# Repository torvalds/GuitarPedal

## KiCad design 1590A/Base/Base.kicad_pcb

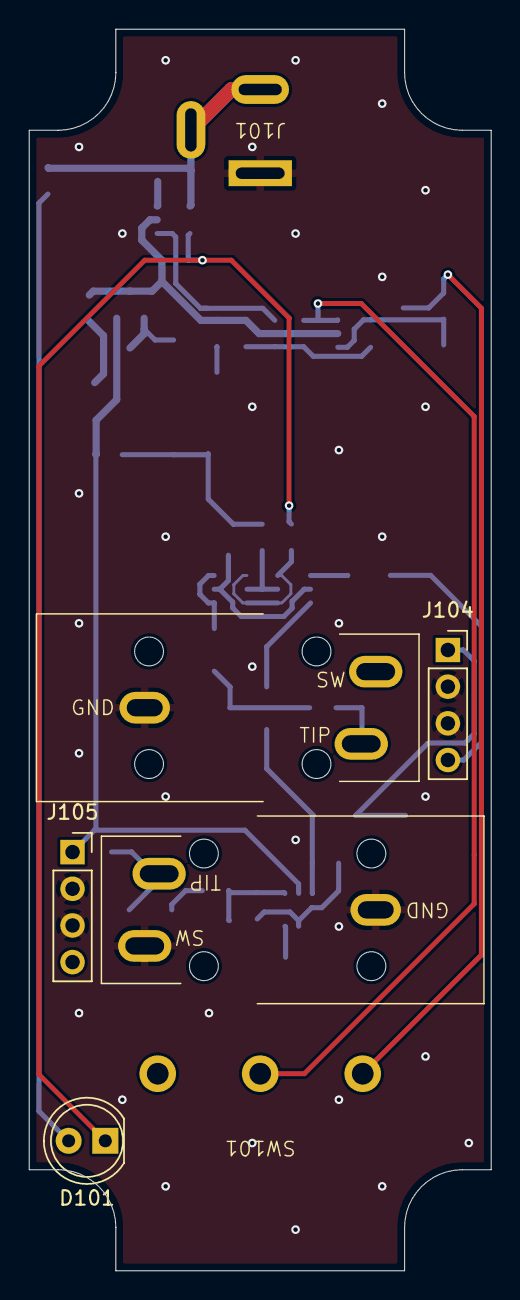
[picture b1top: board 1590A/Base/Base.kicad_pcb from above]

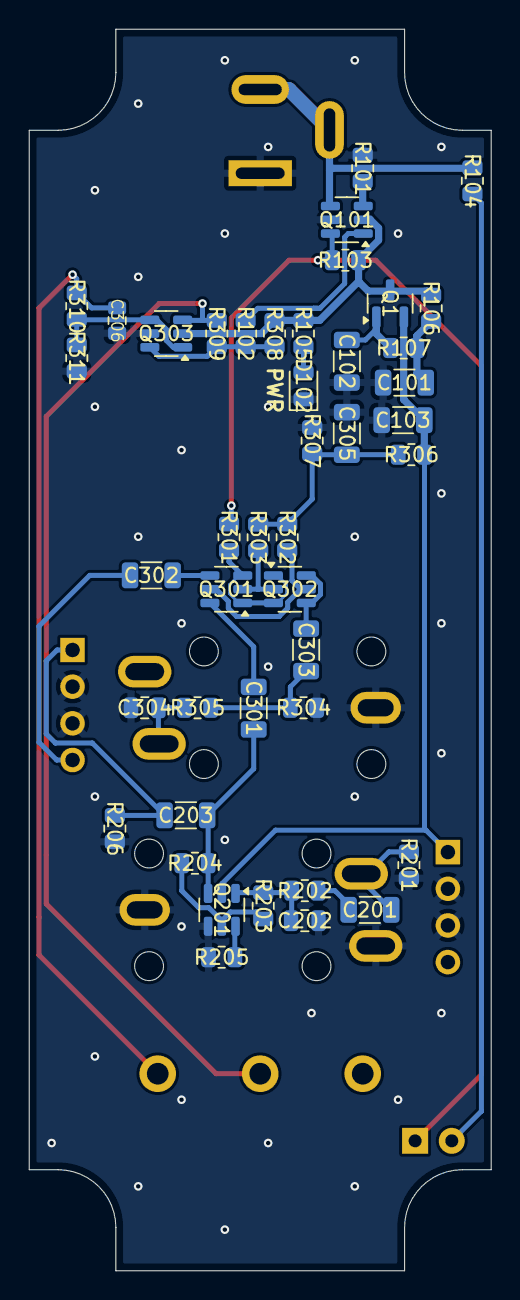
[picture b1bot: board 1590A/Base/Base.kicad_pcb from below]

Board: 2 copper layers, 32.0 x 86.0 mm, 51 parts (43 on the bottom side), 32 nets.

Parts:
Box101: 1590A
C101, C102, C103, C305: 10uF; C_1206_3216Metric
C201, C203: 4.7uF; C_1206_3216Metric
C202: 150pF; C_0805_2012Metric
C301, C302, C303: 1uF; C_1206_3216Metric
C304: 220pF; C_0805_2012Metric
C306: 0.1uF; C_0704_1810Metric
D101: LED; LED_D5.0mm
D102: LED; LED_0805_2012Metric
J101: Barrel_Jack_Switch; Wurth WR-DC 2.1mm Power Jack
J102, J103: AudioJack2_Ground; CK-6.35
J104, J105: Conn_01x04_Pin; PinSocket_1x04_P2.54mm_Vertical
Q1: BC846; SOT-23
Q101, Q301, Q302, Q303: DMC3071LVT; TSOT-23-6
Q201: LS844; SOT-23-6
R101, R102, R103: 100k; R_0805_2012Metric
R104, R105, R106, R107, R305: 2k2; R_0805_2012Metric
R201, R203, R206, R302, R303, R304, R310: 1MEG; R_0805_2012Metric
R202: 1k; R_0805_2012Metric
R204, R205: 1k5; R_0805_2012Metric
R301: 10MEG; R_0805_2012Metric
R306, R307: 4k7; R_0805_2012Metric
R308, R309, R311: 22k; R_0805_2012Metric
SW101: SW_Push_SPDT; PBS-24-102P

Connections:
+VA: C103.1, J105.1, Q1.2 (E), Q201.2 (D), R306.2
BUFFERED: C203.1, C301.1, Q201.3 (S), R204.1
GATE: Q301.1 (G), Q301.3 (G), Q302.1 (G), Q302.3 (G), R301.2
GND: C101.2, C102.2, C103.2, C202.2, C304.2, C305.1, C306.2, D102.1 (K), J101.1, J102.G, J102.S, J103.G, J104.2, J104.3, J105.2, J105.3, Q101.5 (S), Q201.4 (G), Q303.5 (S), R101.2, R201.2, R205.2, R206.2, R304.1, R307.1, R311.1
IN^{CONN}: C201.1, J102.T, R201.1
IN^{EFF}: C203.2, J104.1, R206.1
unnamed: C101.1, R106.2, R107.1
unnamed: C201.2, R202.1
unnamed: C303.2, R304.2, R305.1
unnamed: D101.2 (A), R104.2
unnamed: D102.2 (A), R105.2
unnamed: C102.1, Q1.1 (B), R107.2
unnamed: Q101.1 (G), R102.2
unnamed: Q101.3 (G), R101.1
unnamed: C202.1, Q201.1 (G), R202.2, R203.1
unnamed: Q201.5 (D), R203.2, R204.2
unnamed: Q201.6 (S), R205.1
unnamed: C301.2, Q301.6 (D)
unnamed: Q301.5 (S), Q302.5 (S), R302.1
unnamed: C302.2, Q301.4 (D)
unnamed: Q301.2 (S), Q302.2 (S), R303.2
unnamed: C303.1, Q302.4 (D), Q302.6 (D)
unnamed: Q303.1 (G), Q303.4 (D), R310.2, R311.2
ON_LOW: D101.1 (K), Q101.6 (D), R103.2, R301.1
ON_OFF: Q303.6 (D), R102.1, R308.1, R309.1
OUT^{CONN}: C304.1, J103.T, R305.2
OUT^{EFF}: C302.1, J104.4
PWRIN: J101.2, J101.3, Q101.4 (D), R104.1
SW1: Q303.3 (G), R309.2, SW101.2 (B)
SW2: C306.1, R310.1, SW101.3 (C)
VBIAS: C305.2, R302.2, R303.1, R306.1, R307.2
VIN: Q1.3 (C), Q101.2 (S), Q303.2 (S), R103.1, R105.1, R106.1, R308.2

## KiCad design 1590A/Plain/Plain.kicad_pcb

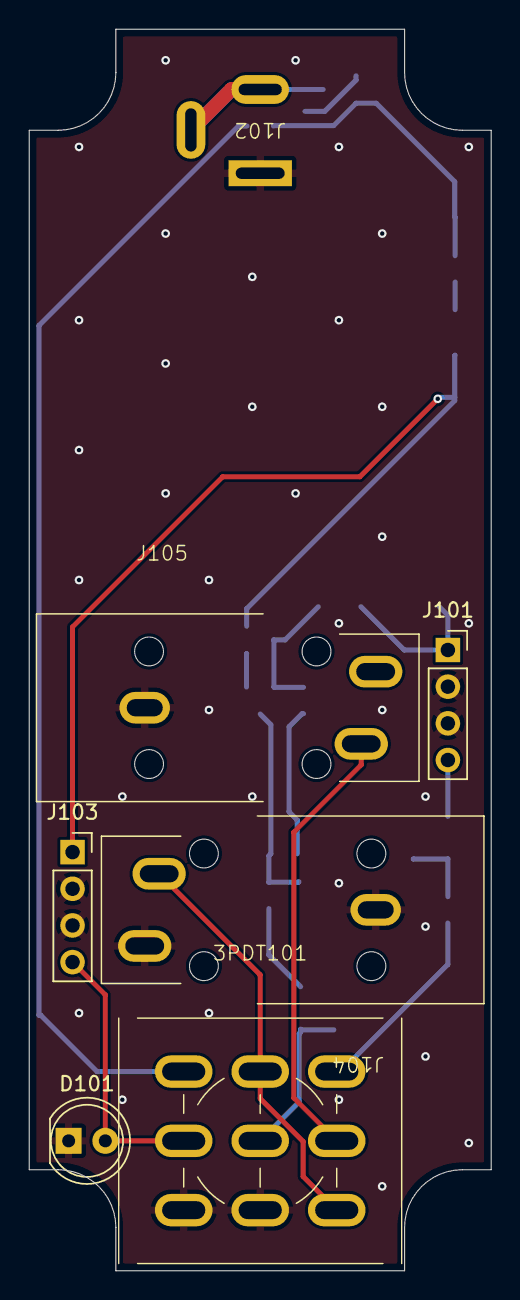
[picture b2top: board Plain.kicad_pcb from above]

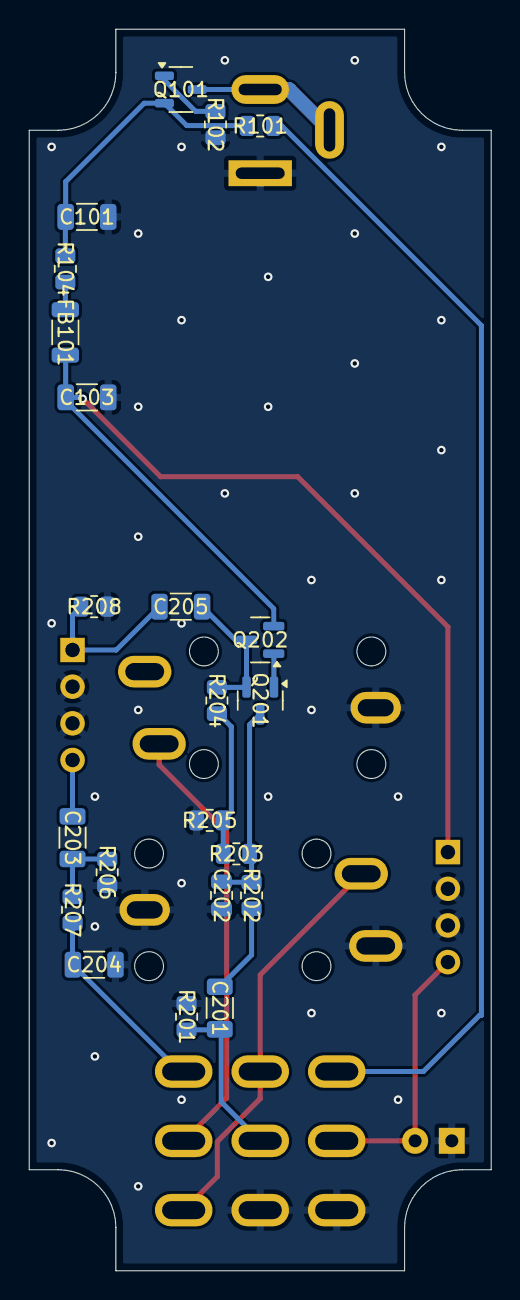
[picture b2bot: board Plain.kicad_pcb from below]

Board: 2 copper layers, 32.0 x 86.0 mm, 30 parts (22 on the bottom side), 20 nets.

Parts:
3PDT101: 3PDT-Stomp-Switch
Box101: 1590A
C101, C103: 22uF; C_1206_3216Metric
C201, C203, C205: 1uF; C_1206_3216Metric
C202: 150pF; C_0805_2012Metric
C204: 1nF; C_1206_3216Metric
D101: LED; LED_D5.0mm
FB101: FerriteBead; L_1206_3216Metric
J101, J103: Conn_01x04_Pin; PinSocket_1x04_P2.54mm_Vertical
J102: Barrel_Jack_Switch; Wurth WR-DC 2.1mm Power Jack
J104: Input; CK-6.35
J105: Output; CK-6.35
Q101: PMV250; SOT-23-3
Q201: MMBF5103; SOT-23
Q202: BC857C; SOT-23
R101, R207: 3k3; R_0805_2012Metric
R102: 100k; R_0805_2012Metric
R104: 100R; R_0805_2012Metric
R201, R203, R206, R208: 1MEG; R_0805_2012Metric
R202: 1k; R_0805_2012Metric
R204, R205: 2k2; R_0805_2012Metric

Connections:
+VA: C103.1, FB101.2, J103.1, Q202.2 (E)
GND: 3PDT101.3 (A3), 3PDT101.6 (B3), C101.2, C103.2, C202.2, C204.1, D101.1 (K), J101.2, J101.3, J102.1, J103.2, J103.3, J104.S, J104.TN, J105.S, R102.2, R201.2, R205.2, R206.2, R208.2
INPUT: 3PDT101.5 (B2), C201.1, R201.1
IN^{CONN}: 3PDT101.4 (B1), 3PDT101.9 (C3), J104.T
IN^{EFF}: C205.2, J101.1, R208.1
LEDPWR: 3PDT101.2 (A2), D101.2 (A), J103.4
unnamed: 3PDT101.1 (A1), R101.1
unnamed: C201.2, R202.1
unnamed: C203.2, R206.1, R207.1
unnamed: FB101.1, R104.2
unnamed: Q101.1 (G), R102.1
unnamed: Q201.1 (D), Q202.1 (B)
unnamed: C202.1, Q201.3 (G), R202.2, R203.1
unnamed: C205.1, Q201.2 (S), Q202.3 (C), R204.1
unnamed: R203.2, R204.2, R205.1
OUTPUT: 3PDT101.7 (C1), C204.2, R207.2
OUT^{CONN}: 3PDT101.8 (C2), J105.T
OUT^{EFF}: C203.1, J101.4
PWRIN: J102.2, J102.3, Q101.3 (D)
VIN: C101.1, Q101.2 (S), R101.2, R104.1

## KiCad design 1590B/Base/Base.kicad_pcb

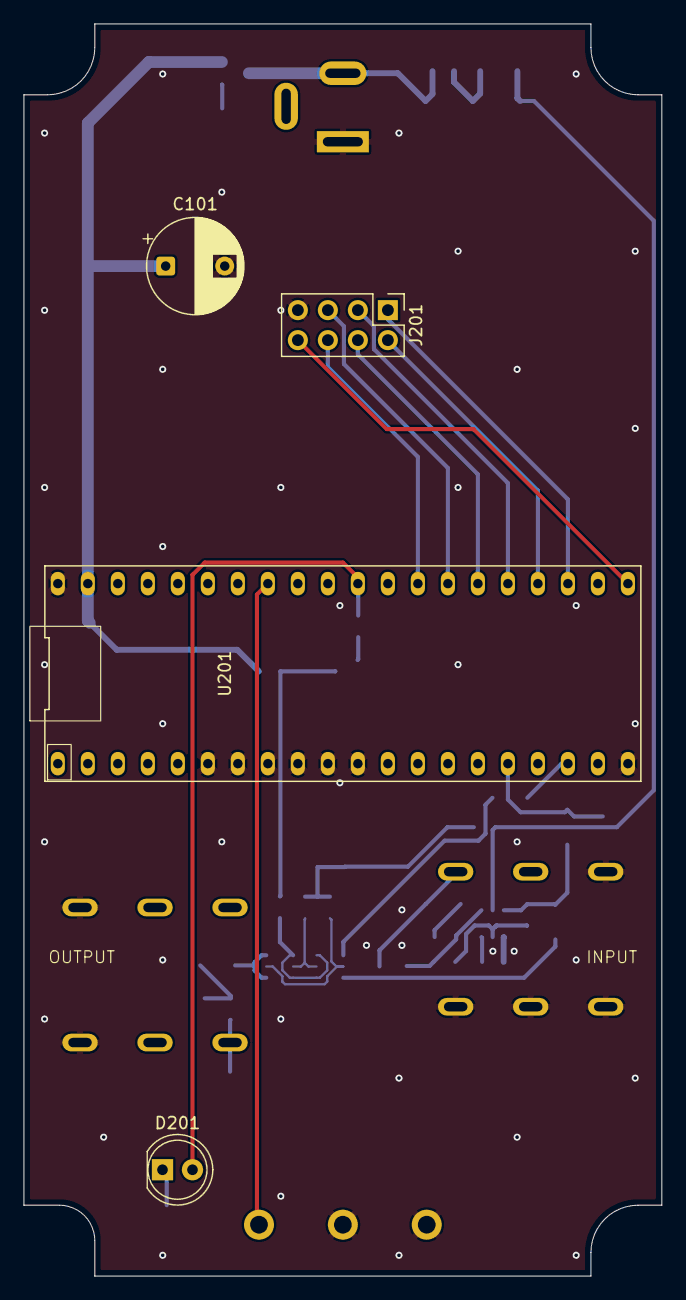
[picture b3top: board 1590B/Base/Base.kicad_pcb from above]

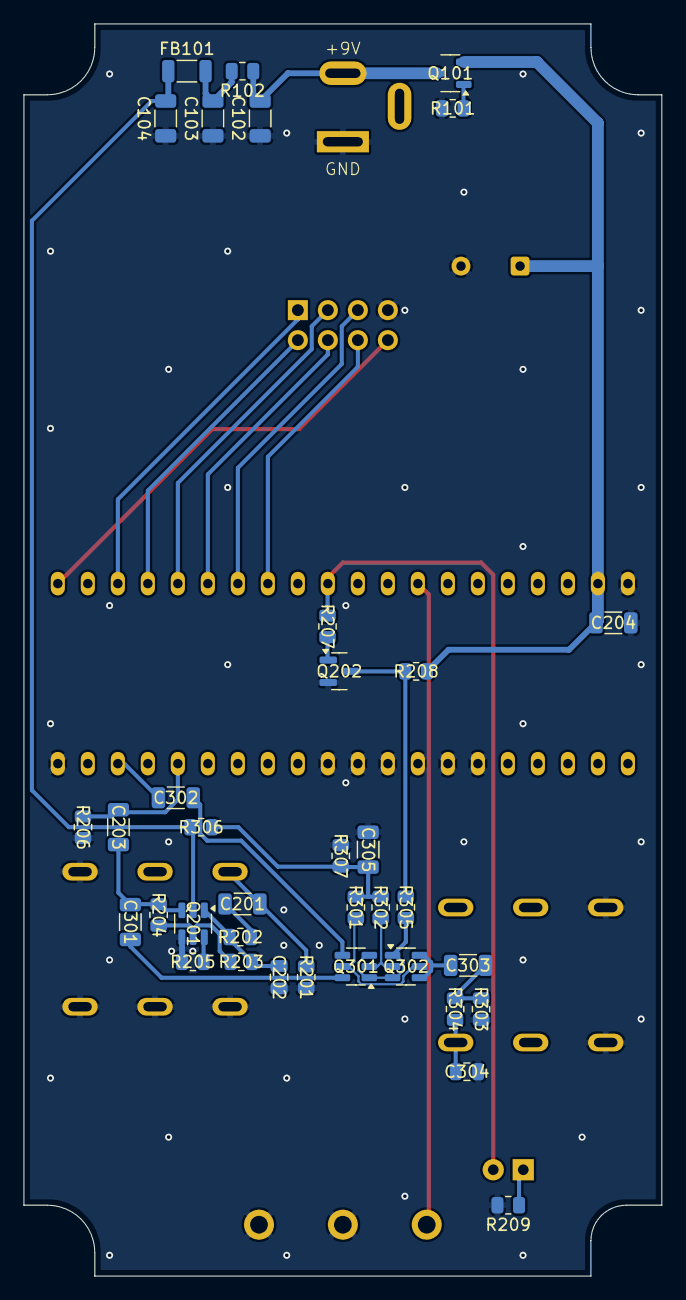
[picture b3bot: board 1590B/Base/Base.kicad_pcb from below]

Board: 2 copper layers, 54.0 x 106.0 mm, 45 parts (36 on the bottom side), 35 nets.

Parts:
Box101: 1590B
C101: 100uF; CP_Radial_D8.0mm_P5.00mm
C102, C103, C305: 10uF; C_1206_3216Metric
C104, C301, C302, C303: 1uF; C_1206_3216Metric
C201, C203: 4.7uF; C_1206_3216Metric
C202: 150pF; C_0805_2012Metric
C204: 47uF; C_1206_3216Metric
C304: 1nF; C_0805_2012Metric
D201: LED; LED_D5.0mm
FB101: FerriteBead; L_1206_3216Metric
J101: Barrel_Jack_Switch; Wurth WR-DC 2.1mm Power Jack
J102, J103: AudioJack3_SwitchTR; NRJ6HM-1-PRE
J201: Conn_02x04_Odd_Even; PinHeader_2x04_P2.54mm_Vertical
Q101: PMV250; SOT-23-3
Q201: LS844; SOT-23-6
Q202: BC846; SOT-23
Q301, Q302: DMC3071LVT; TSOT-23-6
R101, R208: 100k; R_0805_2012Metric
R102: 100R; R_0805_2012Metric
R201, R203, R206, R301, R302, R303: 1MEG; R_0805_2012Metric
R202, R209: 1k; R_0805_2012Metric
R204, R205: 1k5; R_0805_2012Metric
R207: 10k; R_0805_2012Metric
R304: 3k3; R_0805_2012Metric
R305: 10MEG; R_0805_2012Metric
R306, R307: 4k7; R_0805_2012Metric
SW201: SW_Push_SPDT; PBS-24-102P
U201: Daisy Seed; DaisySeed

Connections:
+3.3VA: J201.8, U201.21 (+3V3_A)
+VA: C104.2, FB101.1, Q201.2 (D), R306.2
BUFFERED: C203.1, C301.1, Q201.3 (S), R204.1
FOOTSW: SW201.3 (C), U201.33 (FOOT_SW2)
GATE: Q301.1 (G), Q301.3 (G), Q302.1 (G), Q302.3 (G), R305.2
GND: C101.2, C102.1, C103.1, C104.1, C202.2, C204.2, C304.2, C305.1, J101.1, J102.RN, J102.S, J102.TN, J103.S, J201.7, Q201.4 (G), Q202.2 (E), R101.2, R201.2, R205.2, R206.2, R209.2, R303.1, R307.1, SW201.1 (A), SW201.2 (B), U201.6 (SW3_UP), U201.7 (SW3_DN), U201.8 (SW2_UP), U201.9 (SW2_DN), U201.10 (SW1_UP), U201.11 (SW1_DN), U201.20 (AGND), U201.40 (GND)
IN^{CONN}: C201.1, J102.T, R201.1
IN^{EFF}: C203.2, R206.1, U201.16 (AUDIO_IN_L)
unnamed: C103.2, FB101.2, R102.2
unnamed: C201.2, R202.1
unnamed: C303.2, R303.2, R304.1
unnamed: D201.1 (K), R209.1
unnamed: Q101.1 (G), R101.1
unnamed: C202.1, Q201.1 (G), R202.2, R203.1
unnamed: Q201.5 (D), R203.2, R204.2
unnamed: Q201.6 (S), R205.1
unnamed: Q202.1 (B), R207.2
unnamed: C301.2, Q301.6 (D)
unnamed: Q301.5 (S), Q302.5 (S), R301.1
unnamed: C302.2, Q301.4 (D)
unnamed: Q301.2 (S), Q302.2 (S), R302.2
unnamed: C303.1, Q302.4 (D), Q302.6 (D)
ON_LOW: Q202.3 (C), R208.2, R305.1
ON_OFF: D201.2 (A), R207.1, U201.30 (LED_2)
OUT^{CONN}: C304.1, J103.T, R304.2
OUT^{EFF}: C302.1, U201.18 (AUDIO_OUT_L)
POT1: J201.1, U201.23 (POT1)
POT2: J201.2, U201.24 (POT2)
POT3: J201.3, U201.25 (POT3)
POT4: J201.4, U201.26 (POT4)
POT5: J201.5, U201.27 (POT5)
POT6: J201.6, U201.28 (POT6)
PWRIN: C102.2, J101.2, Q101.3 (D), R102.1
VBIAS: C305.2, R301.2, R302.1, R306.1, R307.2
VIN: C101.1, C204.1, Q101.2 (S), R208.1, U201.39 (V_IN)

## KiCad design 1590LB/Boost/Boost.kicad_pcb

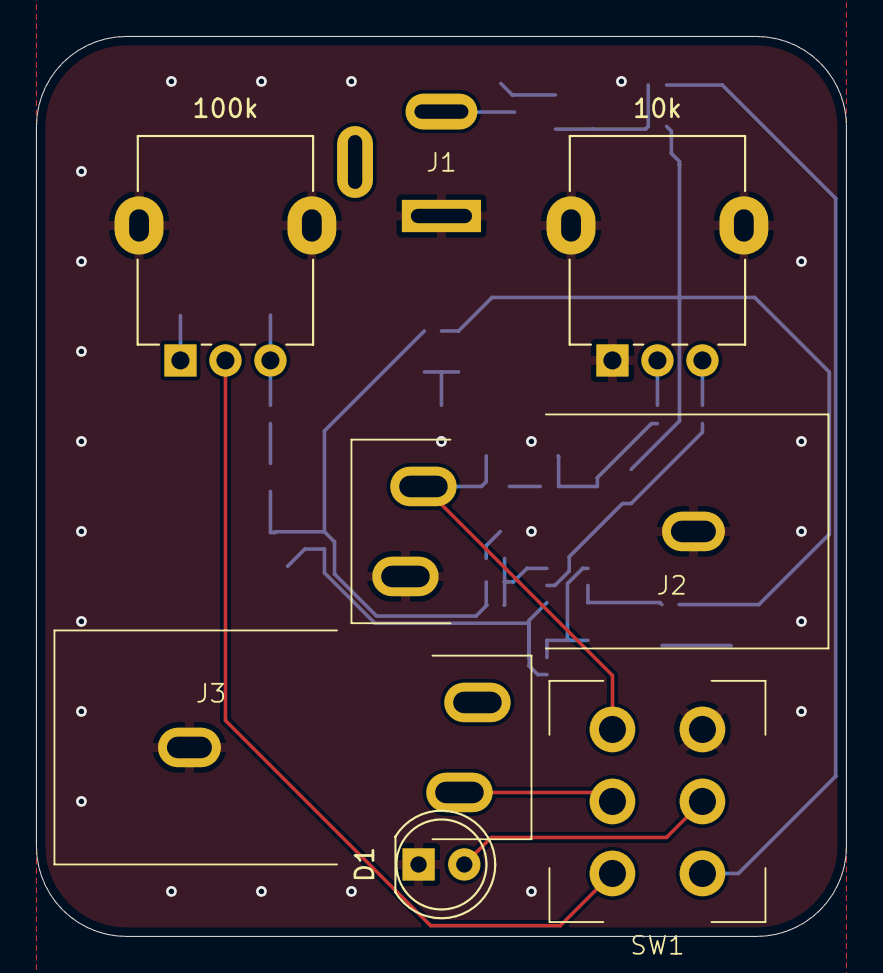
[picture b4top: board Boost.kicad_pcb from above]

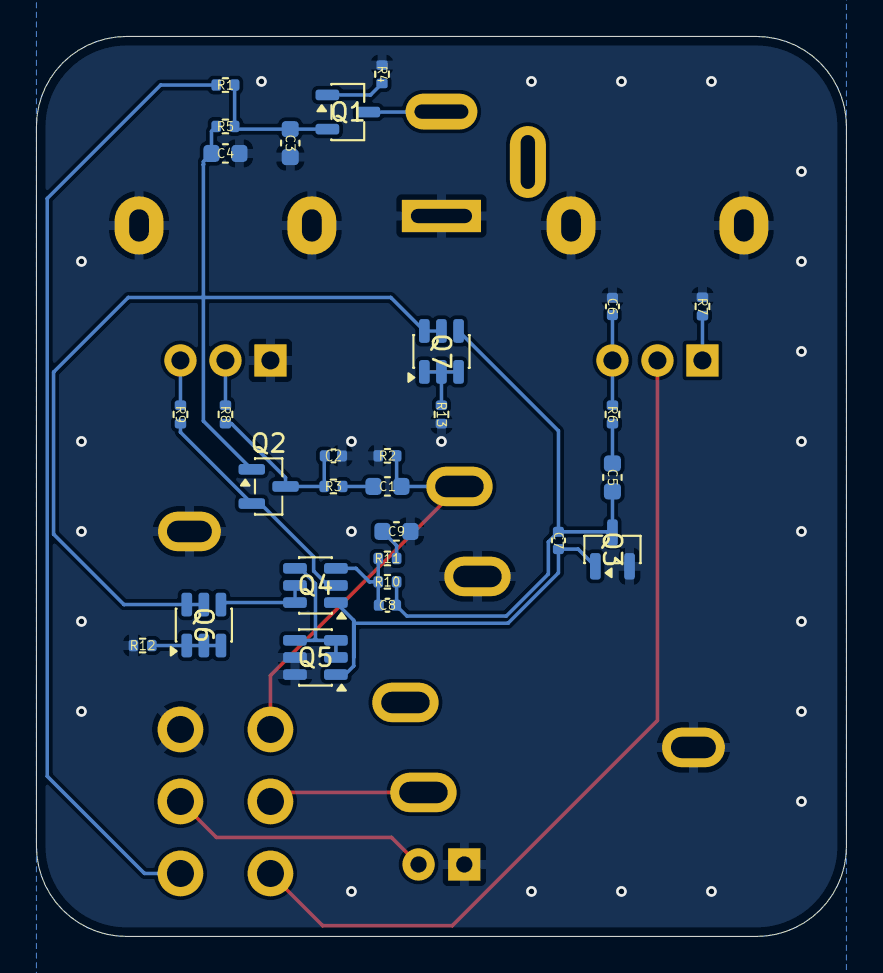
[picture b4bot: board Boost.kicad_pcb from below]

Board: 2 copper layers, 45.0 x 50.0 mm, 36 parts (29 on the bottom side), 26 nets.

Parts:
C1, C5: 1uF; C_0603_1608Metric
C2, C8: 150pF; C_0402_1005Metric
C3, C4, C9: 10uF; C_0603_1608Metric
C6, C7: 1nF; C_0402_1005Metric
D1: LED; LED_D5.0mm
J1: Barrel_Jack_Switch; Wurth WR-DC 2.1mm Power Jack
J2, J3: AudioJack2_SwitchT; CK-6.35-no-NPTH
Q1: PMV250; SOT-23-3
Q2: MMBFJ309L; SOT-23
Q3: BC849C; SOT-23
Q4, Q6, Q7: DMMT5401; SOT-23-6
Q5: DMMT5551; SOT-23-6
R1, R6: 3k3; R_0402_1005Metric
R2, R8: 1MEG; R_0402_1005Metric
R3: 1k; R_0402_1005Metric
R4, R10: 100k; R_0402_1005Metric
R5: 33R; R_0402_1005Metric
R7, R11: 10k; R_0402_1005Metric
R9: 2k2; R_0402_1005Metric
R12, R13: 5k1; R_0402_1005Metric
RV1: 100k; Potentiometer_9mm_MP
RV2: 10k; Potentiometer_9mm_MP
SW1: SW_DPDT_x2; FS5700DPMT2B2M2QE

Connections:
+VA: C4.2, Q2.1 (D), Q6.5 (E), Q6.6 (E), Q7.5 (E), Q7.6 (E), R5.1
BUFFERED: Q2.2 (S), Q4.2 (B), R9.1
FEEDBACK: C8.1, Q4.3 (B), R10.1, R11.1
GND: C2.2, C3.1, C4.1, C6.1, C9.1, D1.1 (K), J1.1, J2.S, J2.TN, J3.S, Q3.2 (E), Q5.5 (E), Q5.6 (E), R2.2, R4.2, R7.2, R12.2, R13.2, RV1.MP (MountPin), RV2.1, RV2.MP (MountPin), SW1.1 (A)
INPUT: C2.1, Q2.3 (G), R3.2, R8.1
IN^{CONN}: C1.1, J2.T, R2.1, SW1.4 (A)
LTP_OUT: C7.2, Q3.1 (B), Q4.1 (C), Q5.1 (C)
unnamed: C1.2, R3.1
unnamed: C5.2, R6.1
unnamed: C6.2, R6.2, RV1.3
unnamed: C9.2, R11.2
unnamed: D1.2 (A), SW1.2 (B)
unnamed: Q1.1 (G), R4.1
unnamed: Q4.4 (C), Q5.2 (B), Q5.3 (B), Q5.4 (C)
unnamed: Q6.1 (C), Q6.2 (B), Q6.3 (B), R12.1
unnamed: Q7.1 (C), Q7.2 (B), Q7.3 (B), R13.1
unnamed: R7.1, RV1.1
unnamed: R8.2, RV2.2
unnamed: R9.2, RV2.3
unnamed: R1.2, SW1.3 (C)
OUTPUT: C5.1, C7.1, C8.2, Q3.3 (C), Q7.4 (C), R10.2
OUT^{CONN}: J3.T, SW1.5 (B)
OUT^{STOMP}: RV1.2, SW1.6 (C)
PWRIN: J1.2, Q1.3 (D)
SRC1: Q4.5 (E), Q4.6 (E), Q6.4 (C)
VIN: C3.2, Q1.2 (S), R1.1, R5.2

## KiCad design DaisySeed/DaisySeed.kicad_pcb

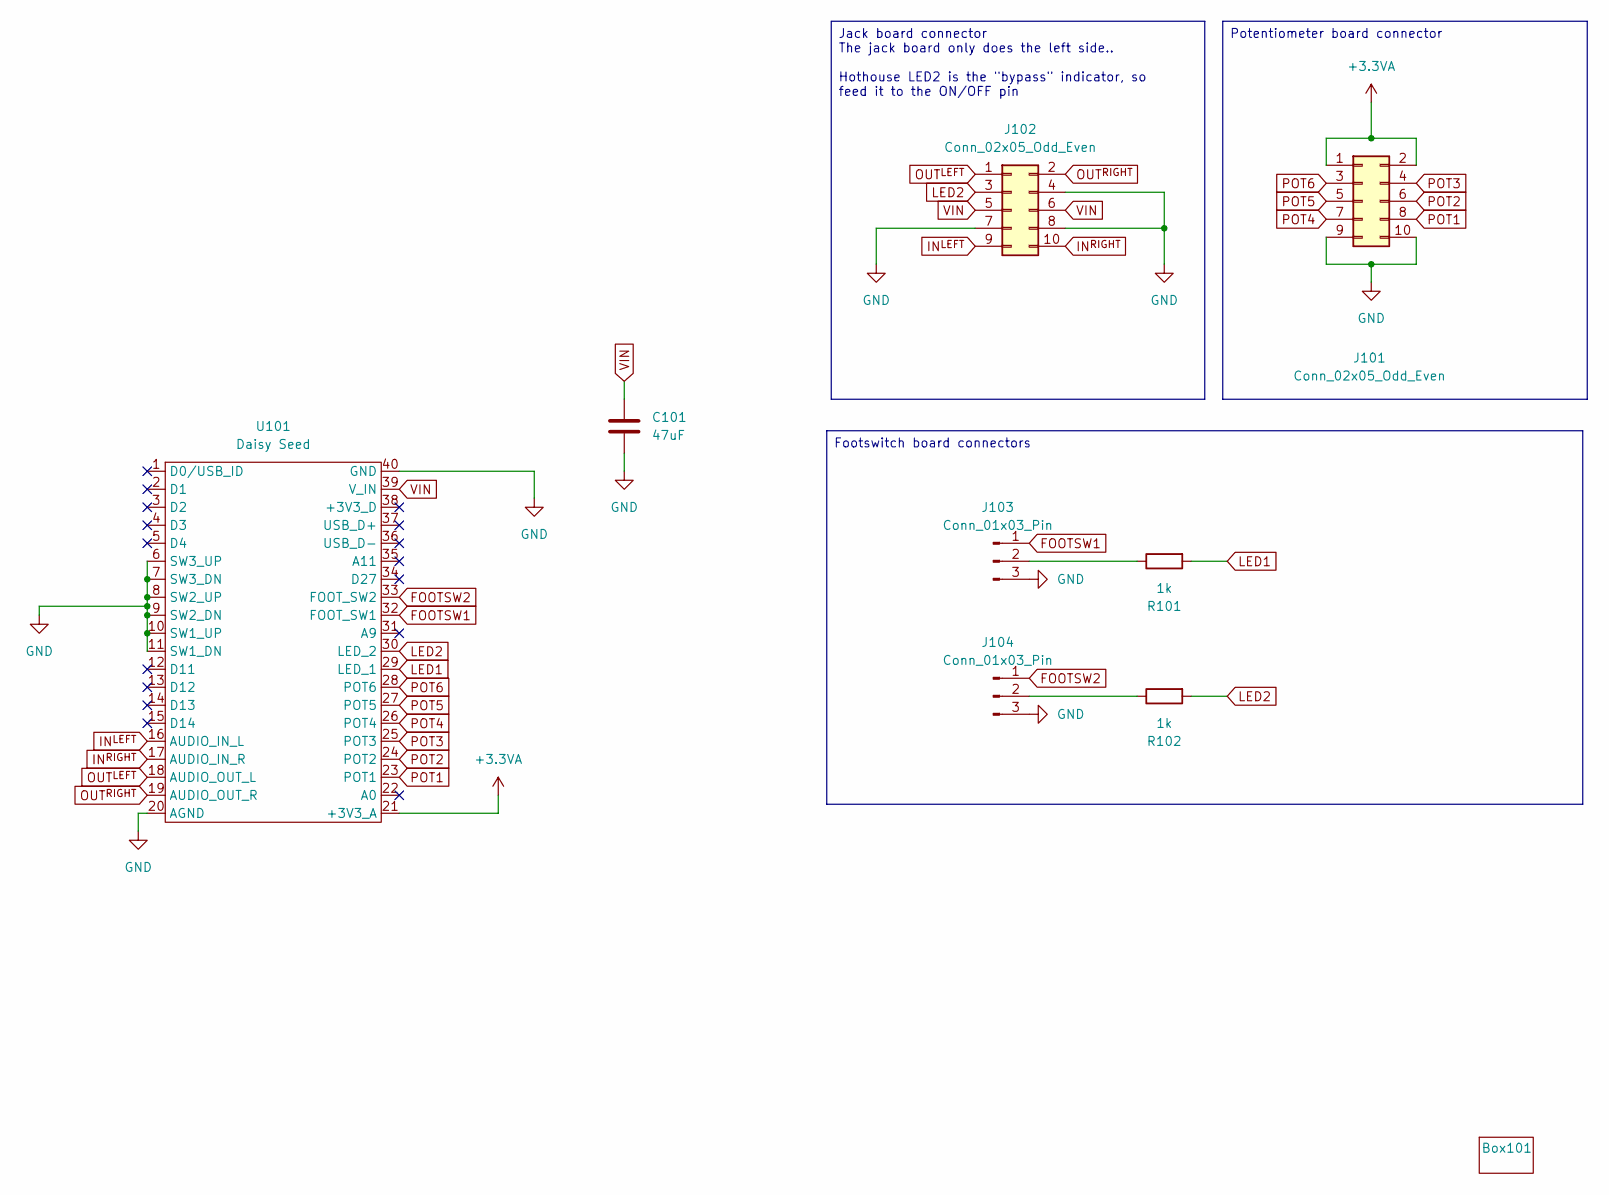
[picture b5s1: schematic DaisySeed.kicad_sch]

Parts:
Box101: 125B
C101: 47uF; C_1206_3216Metric
J101: Conn_02x05_Odd_Even; PinHeader_2x05_P1.27mm_Vertical_SMD
J102: Conn_02x05_Odd_Even; IDC-Header_2x05_P2.54mm_Vertical
J103, J104: Conn_01x03_Pin; JST_ZH_B3B-ZR_1x03_P1.50mm_Vertical
R101, R102: 1k; R_0805_2012Metric
U101: Daisy Seed; DaisySeed

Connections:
+3.3VA: J101.1, J101.2, U101.21 (+3V3_A)
FOOTSW1: J103.1, U101.32 (FOOT_SW1)
FOOTSW2: J104.1, U101.33 (FOOT_SW2)
GND: C101.2, J101.9, J101.10, J102.4, J102.7, J102.8, J103.3, J104.3, U101.6 (SW3_UP), U101.7 (SW3_DN), U101.8 (SW2_UP), U101.9 (SW2_DN), U101.10 (SW1_UP), U101.11 (SW1_DN), U101.20 (AGND), U101.40 (GND)
IN^{LEFT}: J102.9, U101.16 (AUDIO_IN_L)
IN^{RIGHT}: J102.10, U101.17 (AUDIO_IN_R)
LED1: R101.2, U101.29 (LED_1)
LED2: J102.3, R102.2, U101.30 (LED_2)
unnamed: J103.2, R101.1
unnamed: J104.2, R102.1
OUT^{LEFT}: J102.1, U101.18 (AUDIO_OUT_L)
OUT^{RIGHT}: J102.2, U101.19 (AUDIO_OUT_R)
POT1: J101.8, U101.23 (POT1)
POT2: J101.6, U101.24 (POT2)
POT3: J101.4, U101.25 (POT3)
POT4: J101.7, U101.26 (POT4)
POT5: J101.5, U101.27 (POT5)
POT6: J101.3, U101.28 (POT6)
VIN: C101.1, J102.5, J102.6, U101.39 (V_IN)

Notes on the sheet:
Potentiometer board connector
Footswitch board connectors
Jack board connector The jack board only does the left side.. Hothouse LED2 is the "bypass" indicator, so feed it to the ON/OFF pin

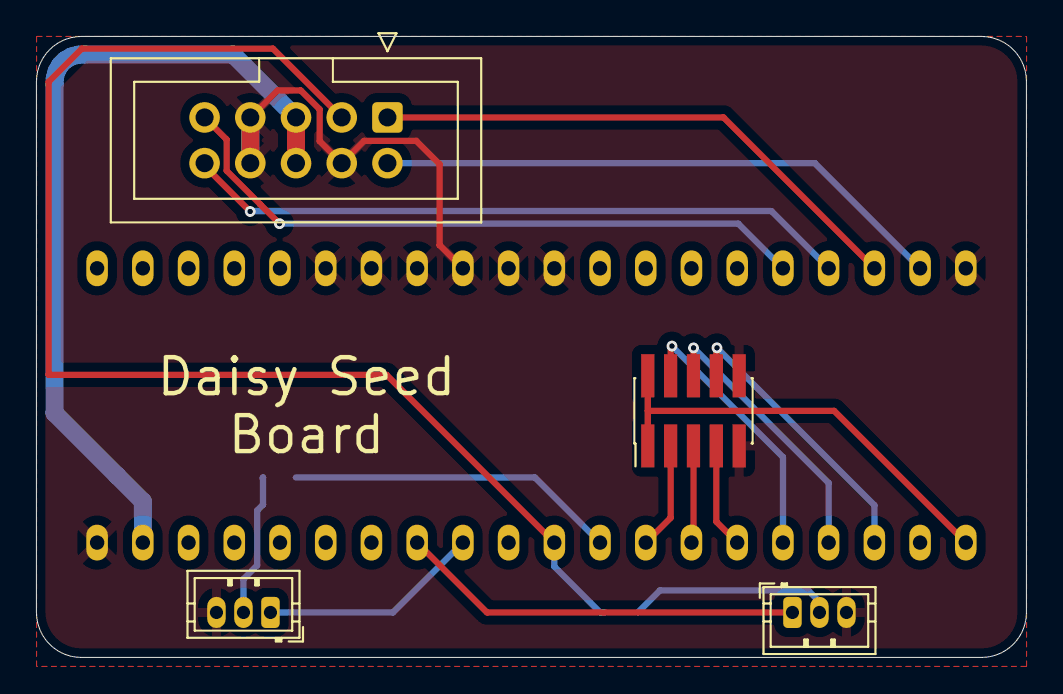
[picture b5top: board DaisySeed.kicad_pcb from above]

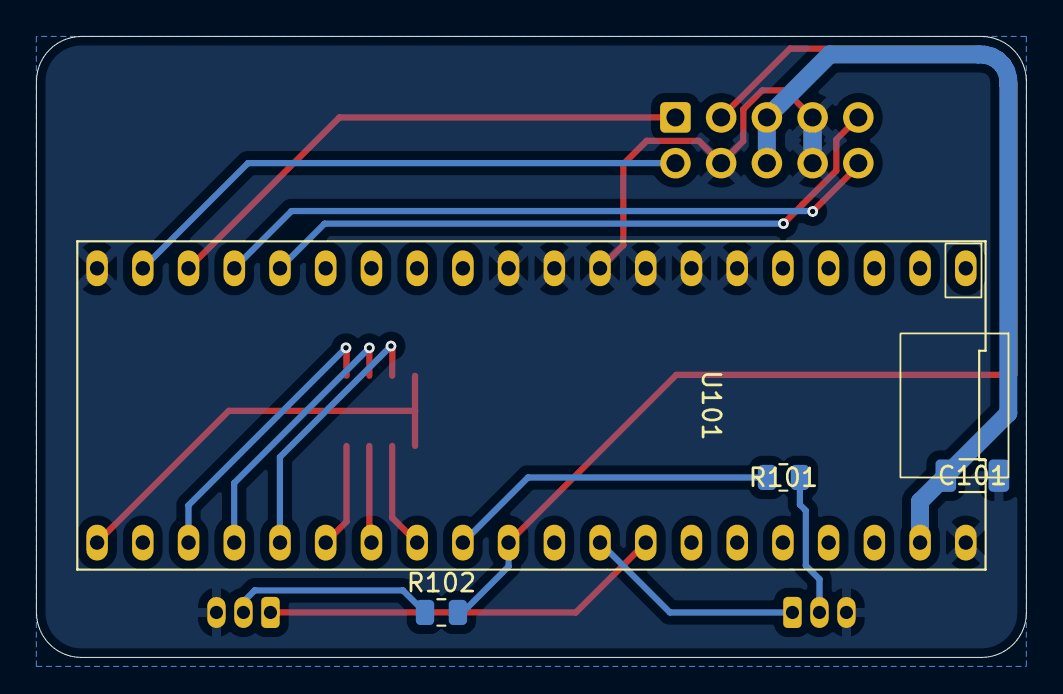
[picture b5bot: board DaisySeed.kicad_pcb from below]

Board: 2 copper layers, 55.0 x 34.5 mm, 9 parts (4 on the bottom side), 19 nets.

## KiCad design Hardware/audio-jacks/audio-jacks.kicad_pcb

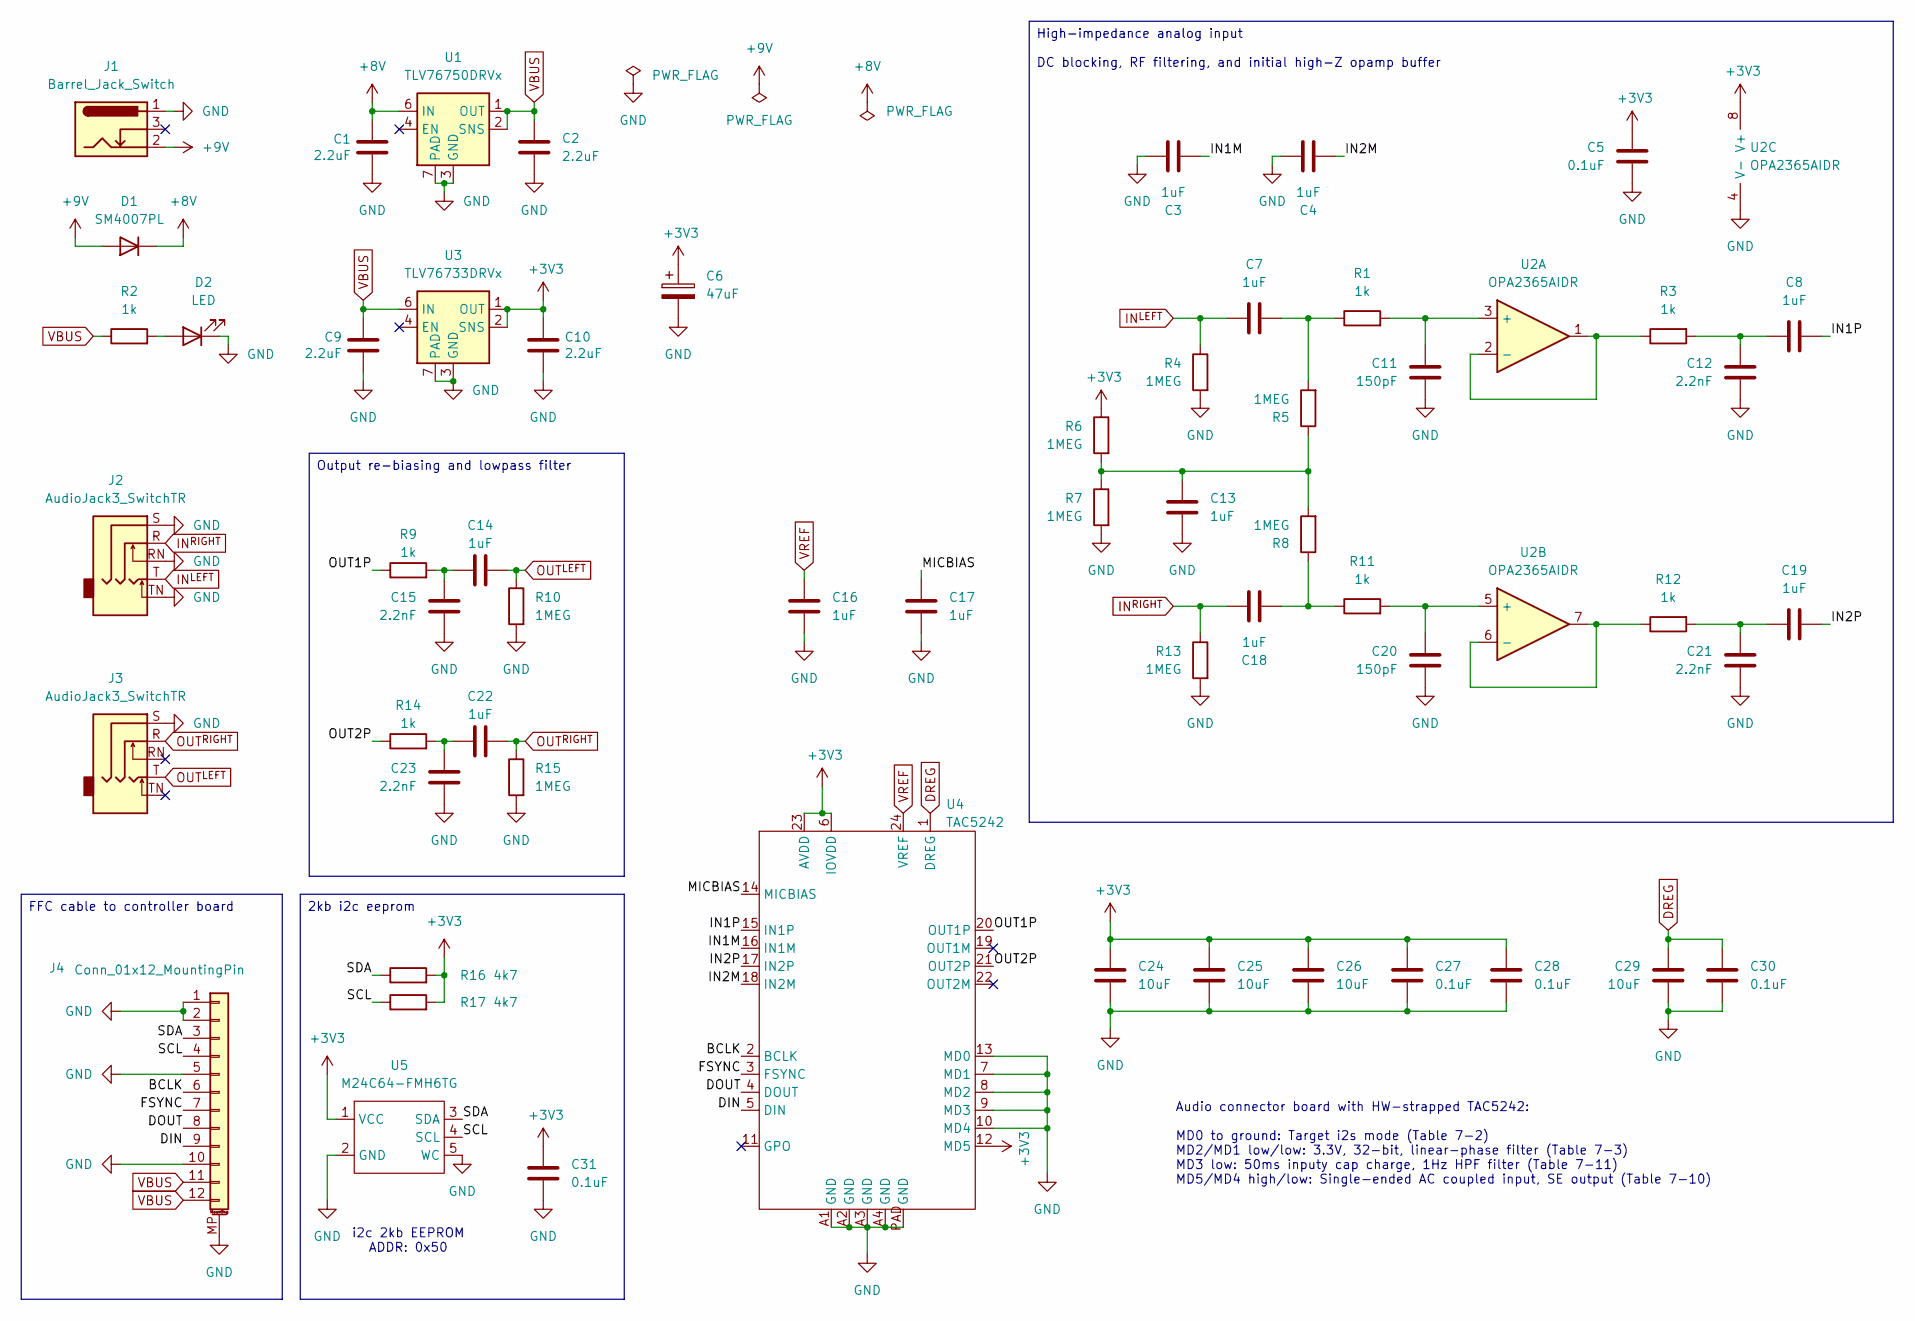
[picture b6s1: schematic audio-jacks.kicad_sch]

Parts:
C1, C2, C9, C10: 2.2uF; C_0805_2012Metric; LCSC PN C77081
C3, C4, C7, C8, C13, C14, C16, C17, C18, C19, C22: 1uF; C_0603_1608Metric; LCSC PN C85862
C5, C27, C28, C30, C31: 0.1uF; C_0402_1005Metric; LCSC PN C1525
C6: 47uF; CP_Elec_6.3x5.9; LCSC PN C178639
C11, C20: 150pF; C_0402_1005Metric; LCSC PN C710836
C12, C15, C21, C23: 2.2nF; C_0402_1005Metric; MANUFACTURER_PART_NUMBER GRM1555C1H222GA01D; LCSC PN C2987940
C24, C25, C26, C29: 10uF; C_0603_1608Metric; LCSC PN C91606
D1: SM4007PL; SOD-123FL; LCSC C64898
D2: LED; LED_0402_1005Metric; LCSC PN C160479
J1: Barrel_Jack_Switch; Wurth WR-DC 2.1mm Power Jack
J2, J3: AudioJack3_SwitchTR; NRJ6HM-1-PRE
J4: Conn_01x12_MountingPin; AFH-5-S12FIA-1H; LCSC PN C5371161
R1, R2, R3, R9, R11, R12, R14: 1k; R_0402_1005Metric; LCSC PN C136974
R4, R5, R6, R7, R8, R10, R13, R15: 1MEG; R_0402_1005Metric; LCSC PN C1884615
R16, R17: 4k7; R_0402_1005Metric; JLCPCB C25900
U1: TLV76750DRVx; WSON-6-1EP_2x2mm_P0.65mm_EP1x1.6mm; LCSC PN C2872569
U2: OPA2365AIDR; SOIC-8_3.9x4.9mm_P1.27mm; JLCPCB C130011
U3: TLV76733DRVx; WSON-6-1EP_2x2mm_P0.65mm_EP1x1.6mm; LCSC PN C2848334
U4: TAC5242; JLCPCB C47122155
U5: M24C64-FMH6TG; UFDFPN5; JLCPCB C222104

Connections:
+3V3: C5.2, C6.1, C10.1, C24.1, C25.1, C26.1, C27.1, C28.1, C31.1, R6.1, R16.2, R17.2, U2.8 (V+), U3.1 (OUT), U3.2 (SNS), U4.6 (IOVDD), U4.12 (MD5), U4.23 (AVDD), U5.1 (VCC)
+8V: C1.1, D1.1 (K), U1.6 (IN)
+9V: D1.2 (A), J1.2
/BCLK: J4.6, U4.2 (BCLK)
/DIN: J4.9, U4.5 (DIN)
/DOUT: J4.8, U4.4 (DOUT)
/FSYNC: J4.7, U4.3 (FSYNC)
/IN1M: C3.2, U4.16 (IN1M)
/IN1P: C8.2, U4.15 (IN1P)
/IN2M: C4.2, U4.18 (IN2M)
/IN2P: C19.2, U4.17 (IN2P)
/MICBIAS: C17.1, U4.14 (MICBIAS)
/OUT1P: R9.1, U4.20 (OUT1P)
/OUT2P: R14.1, U4.21 (OUT2P)
/SCL: J4.4, R17.1, U5.4 (SCL)
/SDA: J4.3, R16.1, U5.3 (SDA)
DREG: C29.1, C30.1, U4.1 (DREG)
GND: C1.2, C2.2, C3.1, C4.1, C5.1, C6.2, C9.2, C10.2, C11.2, C12.1, C13.1, C15.1, C16.2, C17.2, C20.2, C21.1, C23.1, C24.2, C25.2, C26.2, C27.2, C28.2, C29.2, C30.2, C31.2, D2.1 (K), J1.1, J2.RN, J2.S, J2.TN, J3.S, J4.1, J4.2, J4.5, J4.10, J4.MP (MountPin), R4.2, R7.2, R10.2, R13.2, R15.2, U1.3 (GND), U1.5 (GND), U1.7 (PAD), U2.4 (V-), U3.3 (GND), U3.5 (GND), U3.7 (PAD), U4.7 (MD1), U4.8 (MD2), U4.9 (MD3), U4.10 (MD4), U4.13 (MD0), U4.A1 (GND), U4.A2 (GND), U4.A3 (GND), U4.A4 (GND), U4.PAD (GND), U5.2 (GND), U5.5 (WC)
IN^{LEFT}: C7.1, J2.T, R4.1
IN^{RIGHT}: C18.1, J2.R, R13.1
unnamed: C7.2, R1.1, R5.2
unnamed: C8.1, C12.2, R3.2
unnamed: C13.2, R5.1, R6.2, R7.1, R8.2
unnamed: C14.1, C15.2, R9.2
unnamed: C18.2, R8.1, R11.1
unnamed: C19.1, C21.2, R12.2
unnamed: C22.1, C23.2, R14.2
unnamed: D2.2 (A), R2.2
unnamed: C11.1, R1.2, U2.3 (+)
unnamed: R3.1, U2.1, U2.2 (-)
unnamed: C20.1, R11.2, U2.5 (+)
unnamed: R12.1, U2.6 (-), U2.7
OUT^{LEFT}: C14.2, J3.T, R10.1
OUT^{RIGHT}: C22.2, J3.R, R15.1
VBUS: C2.1, C9.1, J4.11, J4.12, R2.1, U1.1 (OUT), U1.2 (SNS), U3.6 (IN)
VREF: C16.1, U4.24 (VREF)

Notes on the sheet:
i2c 2kb EEPROM ADDR: 0x50
Audio connector board with HW-strapped TAC5242: MD0 to ground: Target i2s mode (Table 7-2) MD2/MD1 low/low: 3.3V, 32-bit, linear-phase filter (Table 7-3) MD3 low: 50ms inputy cap charge, 1Hz HPF filter (Table 7-11) MD5/MD4 high/low: Single-ended AC coupled input, SE output (Table 7-10)
2kb i2c eeprom
High-impedance analog input DC blocking, RF filtering, and initial high-Z opamp buffer
FFC cable to controller board
Output re-biasing and lowpass filter

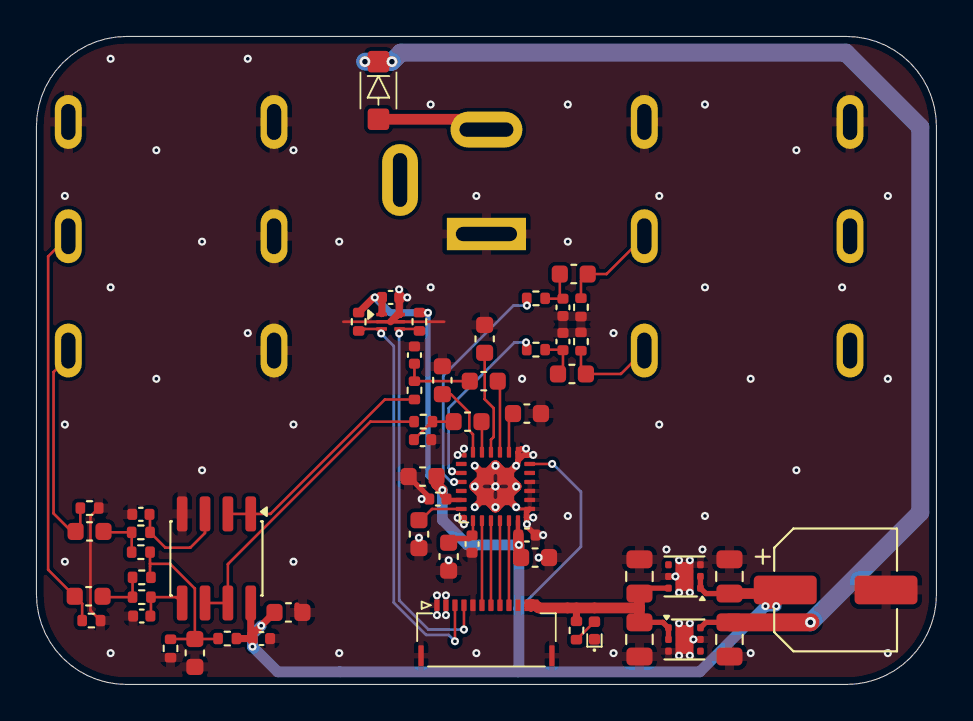
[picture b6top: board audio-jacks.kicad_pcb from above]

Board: 4 copper layers, 50.0 x 36.0 mm, 59 parts (0 on the bottom side), 36 nets.
